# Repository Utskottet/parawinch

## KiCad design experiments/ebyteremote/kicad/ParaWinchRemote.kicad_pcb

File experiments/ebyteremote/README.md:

# ebyteremote — LoRa remote v2 (experiment)

Candidate replacement for the current `remote/` (XIAO nRF52840 + Wio SX1262).
Custom PCB, Ebyte modules:

| | Part | LCSC |
|---|---|---|
| MCU | EBYTE `E73-2G4M08S1C` (nRF52840 module, 43 pins) | `C356849` |
| LoRa | EBYTE `E22-900M30S` | — |

Lives under `experiments/` because it is unproven — no board has been fabricated yet.
It moves up to `remote/` only after the exit criteria below are met.

## Status

Hardware design, pre-fab. Per `docs/Todo.md` (2026-08-12): no board-killers remain;
one schematic edit (D5 flyback diode), BOM bookkeeping, ERC cleanup, and three
ordering decisions outstanding. Layout should not start until ERC is clean.

**`docs/Todo.md` is the authoritative task list.** If any other document here
disagrees with it, Todo.md wins. `docs/FIXLIST.md` is superseded and kept only
for history.

## Layout

```
kicad/          KiCad project — open kicad/ParaWinchRemote.kicad_pro
  lib/          project symbol/footprint/3D libraries, resolved via ${KIPRJMOD}
  backups/      manual pre-change snapshots
  .history/     KiCad local history (gitignored)
docs/           Todo.md, pcb-handoff.md, REMAP-E73.md, ROUTING.md, FIXLIST.md
```

`fp-lib-table`, `sym-lib-table` and `lib/` must stay beside the `.kicad_pro` —
their URIs are `${KIPRJMOD}`-relative, which resolves to the directory holding
the project file. Moving any of them apart breaks every footprint and symbol.

## Exit criteria — what "proven" means

Before this replaces `remote/`:

- [ ] ERC and DRC clean
- [ ] Board fabricated and assembled
- [ ] Firmware brought up: BLE to phone + LoRa link to the winch
- [ ] Range/link budget at least matches the current Wio SX1262 remote, measured, not assumed
- [ ] Full flying session on one charge
- [ ] BLE relay path (phone → remote → winch config) verified end to end

On graduation: tag `remote-xiao-final`, move `remote/` to `archive/remote-xiao/`,
move this folder to `remote/`, update paths in `CLAUDE.md`.

## History

Developed outside the repo in `Documents/EbyteWinchRemote/Vertion 2` and imported
2026-08-16. That folder is the pre-import original and is not the working copy —
this is.

## Known issue

Ten of the 18 footprints in `kicad/lib/parawinch.pretty/` carry absolute 3D model
paths pointing at the old `EbyteWinchRemote/Vertion 2` location. They resolve only
on the original machine while that folder exists, and need rewriting to
`${KIPRJMOD}`-relative.

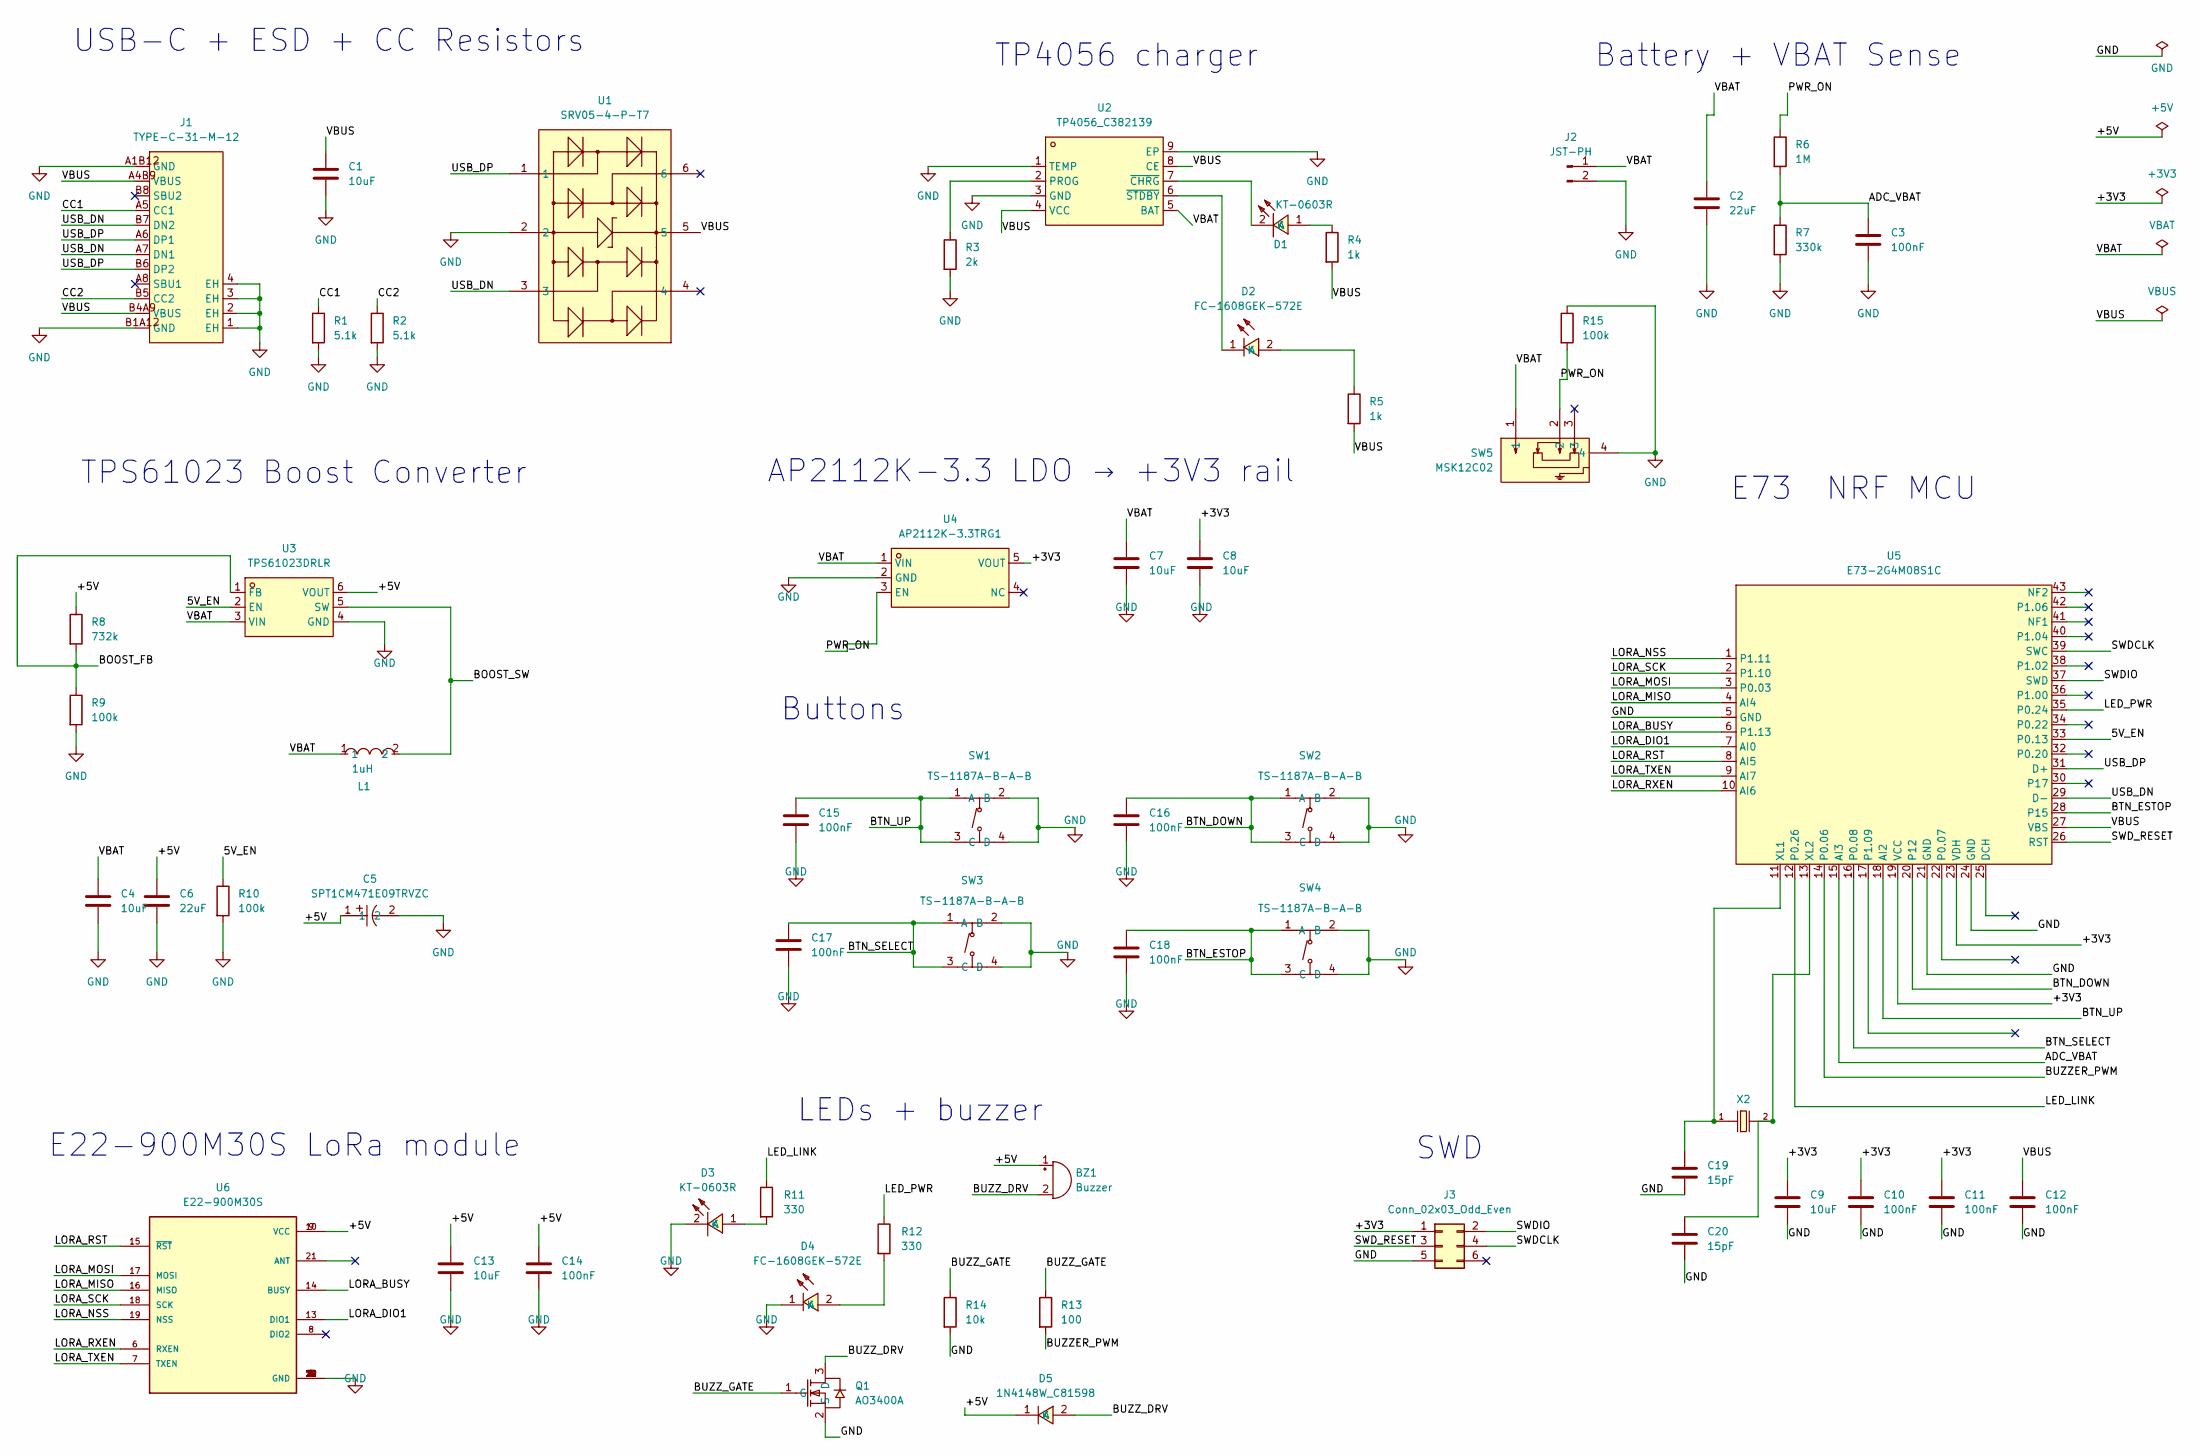
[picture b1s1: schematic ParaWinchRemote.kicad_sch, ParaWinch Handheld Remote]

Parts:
BZ1: Buzzer; Buzzer_12x9.5RM7.6
C1, C4, C7, C8, C9, C13: 10uF; C_0603_1608Metric
C2, C6: 22uF; C_0805_2012Metric
C3, C10, C11, C12, C14, C15, C16, C17, C18: 100nF; C_0603_1608Metric
C5: SPT1CM471E09TRVZC; CAP-SMD_BD6.3-L6.6-W6.6-LS8.0-FD; MPN SPT1CM471E09TRVZC; LCSC Part C22395166
C19, C20: 15pF; C_0603_1608Metric
D1, D3: KT-0603R; LED-SMD_L1.6-W0.8-R-RD; MPN KT-0603R; LCSC Part C2286
D2, D4: FC-1608GEK-572E; LED0603-RD; MPN NCD0603C3; LCSC Part C89809
D5: 1N4148W_C81598; SOD-123F_L2.7-W1.6-LS3.8-RD; MPN 1N4148W; LCSC Part C81598
J1: TYPE-C-31-M-12; USB-C_SMD-TYPE-C-31-M-12_1; MPN TYPE-C-31-M-12; LCSC Part C165948
J2: JST-PH; JST_PH_S2B-PH-K_1x02_P2.00mm_Horizontal
J3: Conn_02x03_Odd_Even; PinHeader_2x03_P2.54mm_Vertical
L1: 1uH; IND-SMD_L4.0-W4.0_LQH44PN2R2MP0L; MPN SWPA4020S1R0NT; LCSC Part C91254
Q1: AO3400A; SOT-23-3_L2.9-W1.3-P1.90-LS2.4-BR; MPN AO3400A; LCSC Part C20917
R1, R2: 5.1k; R_0603_1608Metric
R3: 2k; R_0603_1608Metric
R4, R5: 1k; R_0603_1608Metric
R6: 1M; R_0603_1608Metric
R7: 330k; R_0603_1608Metric
R8: 732k; R_0603_1608Metric
R9, R10, R15: 100k; R_0603_1608Metric
R11, R12: 330; R_0603_1608Metric
R13: 100; R_0603_1608Metric
R14: 10k; R_0603_1608Metric
SW1, SW2, SW3, SW4: TS-1187A-B-A-B; SW-SMD_4P-L5.1-W5.1-P3.70-LS6.5-TL_H1.5; MPN TS-1187A-B-A-B; LCSC Part C318884
SW5: MSK12C02; SW-TH_MSK12C02; MPN MSK12C02; LCSC Part C431540
U1: SRV05-4-P-T7; SOT-23-6_L2.9-W1.6-P0.95-LS2.8-BR; MPN SRV05-4-P-T7; LCSC Part C85364
U2: TP4056_C382139; ESOP-8_L4.9-W3.9-P1.27-LS6.0-BL-EP; MPN TP4056; LCSC Part C382139
U3: TPS61023DRLR; SOT-563_L1.6-W1.2-P0.50-LS1.6-BR; MPN TPS61023DRLR; LCSC Part C919459
U4: AP2112K-3.3TRG1; SOT-25-5_L2.9-W1.6-P0.95-LS2.8-BL; MPN AP2112K-3.3TRG1; LCSC Part C51118
U5: E73-2G4M08S1C; WIRELM-SMD_E73-2G4M08S1C; MPN E73-2G4M08S1C; LCSC Part C356849
U6: E22-900M30S; XCVR_E22-900M30S; PARTREV 1.2
X2: Q13FC1350000400; FC-135R_L3.2-W1.5; Frequency Tolerance ±20ppm; Part Q13FC13500004; LCSC C32346

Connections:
/5V_EN: R10.1, U3.2 (EN), U5.33 (P0.13)
/+3V3: C8.1, C9.1, C10.1, C11.1, J3.1, U4.5 (VOUT), U5.19 (VCC), U5.23 (VDH)
/+5V: BZ1.1 (+), C5.1, C6.1, C13.1, C14.1, D5.1 (K), R8.1, U3.6 (VOUT), U6.9 (VCC), U6.10 (VCC)
/ADC_VBAT: C3.1, R6.2, R7.1, U5.15 (AI3)
/BOOST_FB: R8.2, R9.1, U3.1 (FB)
/BOOST_SW: L1.2, U3.5 (SW)
/BTN_DOWN: C16.1, SW2.1 (A), SW2.3 (C), U5.20 (P12)
/BTN_ESTOP: C18.1, SW4.1 (A), SW4.3 (C), U5.28 (P15)
/BTN_SELECT: C17.1, SW3.1 (A), SW3.3 (C), U5.16 (P0.08)
/BTN_UP: C15.1, SW1.1 (A), SW1.3 (C), U5.18 (AI2)
/BUZZER_PWM: R13.2, U5.14 (P0.06)
/BUZZ_DRV: BZ1.2 (-), D5.2 (A), Q1.3 (D)
/BUZZ_GATE: Q1.1 (G), R13.1, R14.1
/CC1: J1.A5 (CC1), R1.1
/CC2: J1.B5 (CC2), R2.1
/LED_LINK: R11.1, U5.12 (P0.26)
/LED_PWR: R12.1, U5.35 (P0.24)
/LORA_BUSY: U5.6 (P1.13), U6.14 (BUSY)
/LORA_DIO1: U5.7 (AI0), U6.13 (DIO1)
/LORA_MISO: U5.4 (AI4), U6.16 (MISO)
/LORA_MOSI: U5.3 (P0.03), U6.17 (MOSI)
/LORA_NSS: U5.1 (P1.11), U6.19 (NSS)
/LORA_RST: U5.8 (AI5), U6.15 (~RST)
/LORA_RXEN: U5.10 (AI6), U6.6 (RXEN)
/LORA_SCK: U5.2 (P1.10), U6.18 (SCK)
/LORA_TXEN: U5.9 (AI7), U6.7 (TXEN)
/PWR_ON: R6.1, R15.2, SW5.2, U4.3 (EN)
/SWDCLK: J3.4, U5.39 (SWC)
/SWDIO: J3.2, U5.37 (SWD)
/SWD_RESET: J3.3, U5.26 (RST)
/USB_DN: J1.A7 (DN1), J1.B7 (DN2), U1.3, U5.29 (D-)
/USB_DP: J1.A6 (DP1), J1.B6 (DP2), U1.1, U5.31 (D+)
/VBAT: C2.1, C4.1, C7.1, J2.1, L1.1, SW5.1, U2.5 (BAT), U3.3 (VIN), U4.1 (VIN)
/VBUS: C1.1, C12.1, J1.A4B9 (VBUS), J1.B4A9 (VBUS), R4.2, R5.2, U1.5, U2.4 (VCC), U2.8 (CE), U5.27 (VBS)
GND: C1.2, C2.2, C3.2, C4.2, C5.2, C6.2, C7.2, C8.2, C9.2, C10.2, C11.2, C12.2, C13.2, C14.2, C15.2, C16.2, C17.2, C18.2, C19.2, C20.2, D3.2 (K), D4.1 (K), J1.1 (EH), J1.2 (EH), J1.3 (EH), J1.4 (EH), J1.A1B12 (GND), J1.B1A12 (GND), J2.2, J3.5, Q1.2 (S), R1.2, R2.2, R3.2, R7.2, R9.2, R10.2, R14.2, R15.1, SW1.2 (B), SW1.4 (D), SW2.2 (B), SW2.4 (D), SW3.2 (B), SW3.4 (D), SW4.2 (B), SW4.4 (D), SW5.4, U1.2, U2.1 (TEMP), U2.3 (GND), U2.9 (EP), U3.4 (GND), U4.2 (GND), U5.5 (GND), U5.21 (GND), U5.24 (GND), U6.1 (GND), U6.2 (GND), U6.3 (GND), U6.4 (GND), U6.5 (GND), U6.11 (GND), U6.12 (GND), U6.20 (GND), U6.22 (GND)
unnamed: D1.1 (A), R4.1
unnamed: D1.2 (K), U2.7 (~CHRG)
unnamed: D2.2 (A), R5.1
unnamed: D2.1 (K), U2.6 (~STDBY)
unnamed: D3.1 (A), R11.2
unnamed: D4.2 (A), R12.2
unnamed: R3.1, U2.2 (PROG)
unnamed: C19.1, U5.11 (XL1), X2.1
unnamed: C20.1, U5.13 (XL2), X2.2

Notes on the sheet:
LEDs + buzzer
Buttons
E73 NRF MCU
TP4056 charger
USB-C + ESD + CC Resistors
Battery + VBAT Sense
SWD
E22-900M30S LoRa module
TPS61023 Boost Converter
AP2112K-3.3 LDO → +3V3 rail

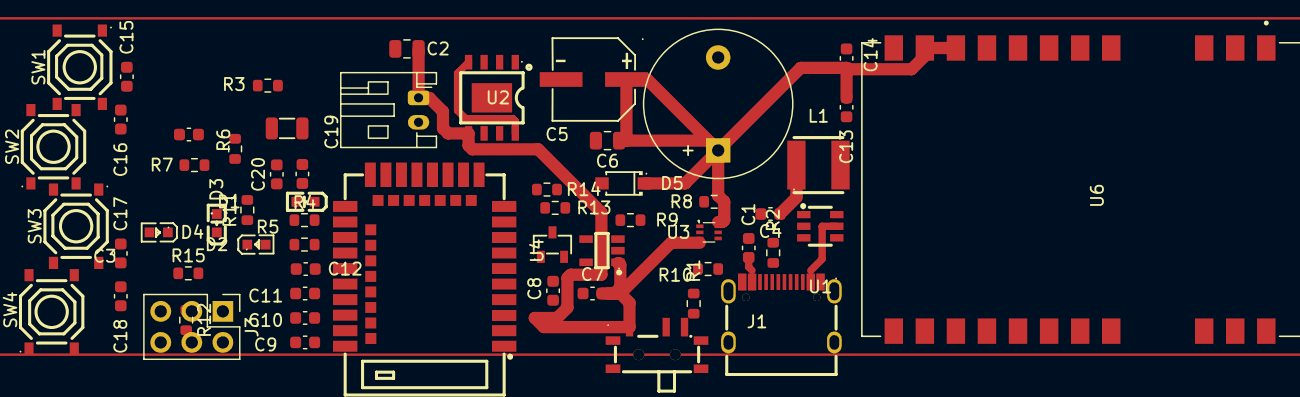
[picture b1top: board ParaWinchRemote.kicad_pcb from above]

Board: 2 copper layers, 58 parts (0 on the bottom side), 44 nets.

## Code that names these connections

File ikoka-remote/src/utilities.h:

#pragma once
/*----------------------------------------------------------
 *  Fork Ikoka Nano — Seeed XIAO nRF52840 Plus + EBYTE E22-900M30S
 *  Pin mapping: SEEED_XIAO_NRF52840_PLUS variant
 *  Source: "Fork Ikoka Nano.kicad_pcb" netlist (U1 pad -> net)
 *
 *  Differences vs. remote/src/utilities.h (XIAO + Wio SX1262 B2B):
 *    - LoRa moves off the B2B pins onto D0-D3 / D7
 *    - buzzer moves off D7 onto the J4 piezo pair D18/D19
 *    - buttons move off D6/D0 onto the J1 header D11/D12
 *---------------------------------------------------------*/

// ═══════════════════════════════════════════════════════
// LoRa E22-900M30S (SX1262 + PA + LNA)
// U1 pad  -> net           -> E22 pin
//   D0    -> SX126X_CS     -> 19 NSS
//   D1    -> SX126X_DIO1   -> 13 DIO1
//   D2    -> SX126X_BUSY   -> 14 BUSY
//   D3    -> SX126X_RESET  -> 15 NRST   (also MT3608B boost EN, see below)
//   D7    -> SX126X_RXEN   ->  6 RXEN
// E22 TXEN (7) is bonded to E22 DIO2 (8) on the PCB — the SX1262 drives its
// own TX enable, so there is no MCU pin for it (setDio2AsRfSwitch).
// ═══════════════════════════════════════════════════════
#define LORA_CS_PIN     D0    // SPI Chip Select
#define LORA_DIO1_PIN   D1    // IRQ / interrupt
#define LORA_BUSY_PIN   D2    // Busy signal
#define LORA_RST_PIN    D3    // Reset  + E22 5 V rail enable
#define LORA_RXEN_PIN   D7    // RX/TX switch: HIGH = RX, LOW = TX

// SPI bus pins (standard XIAO SPI, unchanged from the Wio build)
#define LORA_SCK_PIN    D8
#define LORA_MOSI_PIN   D10
#define LORA_MISO_PIN   D9

// The E22 runs off VCC_E22, a ~5.2 V MT3608B boost whose EN pin is tied to
// SX126X_RESET. Reset asserted (LOW) therefore also cuts the module's supply:
//   RST HIGH -> boost on  -> E22 powered
//   RST LOW  -> boost off -> E22 completely unpowered (300k pulldown = default)
// Nothing to do at runtime beyond letting the rail settle before the first SPI
// transaction, and pulling RST low again on the way into System OFF.
#define LORA_BOOT_SETTLE_MS  10

// ═══════════════════════════════════════════════════════
// Silkscreen pads -> BSP pin indices
//
// Careful: on the XIAO nRF52840 Plus, Seeed's BSP macros D17 and D19 do NOT
// match the pads printed on the board. That pair is swapped:
//
//   silkscreen pad      real GPIO    BSP index    BSP macro claims
//   ---------------     ---------    ---------    ----------------
//   D17                 P1.03           38        D19
//   D18                 P1.05           37        D18          (agrees)
//   D19                 P1.07           36        D17
//
// Verified on hardware with the selftest build: driving the J4 piezo's first
// leg (KiCad pad "D18") works on BSP 37, and the circuit only completes when
// BSP 36 is grounded -- BSP 38 grounded is silent. So the pad the KiCad
// netlist calls "D19" is physically P1.07 = BSP 36.
//
// The KiCad netlist names pads by silkscreen, so these PAD_* names follow the
// silkscreen too and the table above is the only place the swap is handled.
// Never use the bare D17/D19 macros on this board.
// ═══════════════════════════════════════════════════════
#define PAD_D11         D11   // 30, P0.15  -- BSP and silkscreen agree
#define PAD_D12         D12   // 31, P0.19  -- agree
#define PAD_D13         D13   // 32, P1.01  -- agree
#define PAD_D17          38   // P1.03      -- NOT the BSP's D17
#define PAD_D18         D18   // 37, P1.05  -- agree
#define PAD_D19          36   // P1.07      -- NOT the BSP's D19

// ═══════════════════════════════════════════════════════
// Buttons — J1 header (1=BUTTON_1 .. 4=BUTTON_4, 5=GND)
//   J1-1 -> pad D11 (P0.15)   UP     confirmed on hardware
//   J1-2 -> pad D12 (P0.19)   DOWN   confirmed on hardware
//   J1-3 -> pad D13 (P1.01), J1-4 -> pad D17 (P1.03) spare, both untested
// Active LOW against J1-5, internal pullups.
// ═══════════════════════════════════════════════════════
#define BTN_UP_PIN      PAD_D11   // UP: increment state
#define BTN_DN_PIN      PAD_D12   // DOWN: decrement / emergency stop

// ═══════════════════════════════════════════════════════
// Buzzer — J4 piezo, one leg per pin through a 100R series resistor
//   pad D18 (P1.05) -> R4 -> PIEZO_A   driven by tone()
//   pad D19 (P1.07) -> R5 -> PIEZO_B   held LOW as the return path
// Single-ended drive, same as the Wio build's single buzzer pin. High drive
// mode matters here -- at default drive strength the piezo is barely audible.
// ═══════════════════════════════════════════════════════
#define BUZZER_PIN      PAD_D18   // tone() output
#define BUZZER_GND_PIN  PAD_D19   // piezo return, parked LOW

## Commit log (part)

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2026-05-02 Document battery fixes and deep sleep implementation
    Summarize battery voltage calculation issues and proposed fixes for the ParaWinch Remote.
